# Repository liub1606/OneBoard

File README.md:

# OneBoard

OneBoard is a 20(ish) percent keyboard with a rotary encoder. It uses QMK firmware running on a RP2040.

## Features:
- 3D printed outer case
- EC11 Rotary encoder for volume and general media control.
- 19 Keys

## CAD Model:
We use 4 M3 Bolts and heatset inserts to put everything together. In total it has 2 separate peices.

Made using Onshape: https://cad.onshape.com/documents/e6a77505b9b66916f410a9e2/w/3fad1cba9b12220fb1d6acfb/e/3a9642192f18001e0b7e9c0b?renderMode=0&uiState=69bc452a0bbfb517c13afba3

## PCB
My PCB made in Kicad. I used KLE to design the keyboard layout and used a plugin to get everything laid out.

Schematic

PCB

## Firmware Overview
This keyboard uses [QMK](https://qmk.fm/) firmware for everything. 

- The rotary encoder changes volume, press the encoder to pause media.
- Basically acts like the left side of a full sized keyboard.

## BOM:
All the materials needed for this hackpad:
- 19x Cherry MX Switches (16 supplied by Hackclub)
- 19x DSA Keycaps (16 supplied by Hackclub)
- 4x M3x5x4 Heatset inserts
- 4x M3x16mm SHCS Bolts
- 20x 1N4148 DO-35 Diodes. (16 supplied by Hackclub)
- 1x EC11 Rotary Encoder (supplied by Hackclub)
- 1x XIAO RP2040 (supplied by Hackclub)
- 1x Case (2 printed parts)

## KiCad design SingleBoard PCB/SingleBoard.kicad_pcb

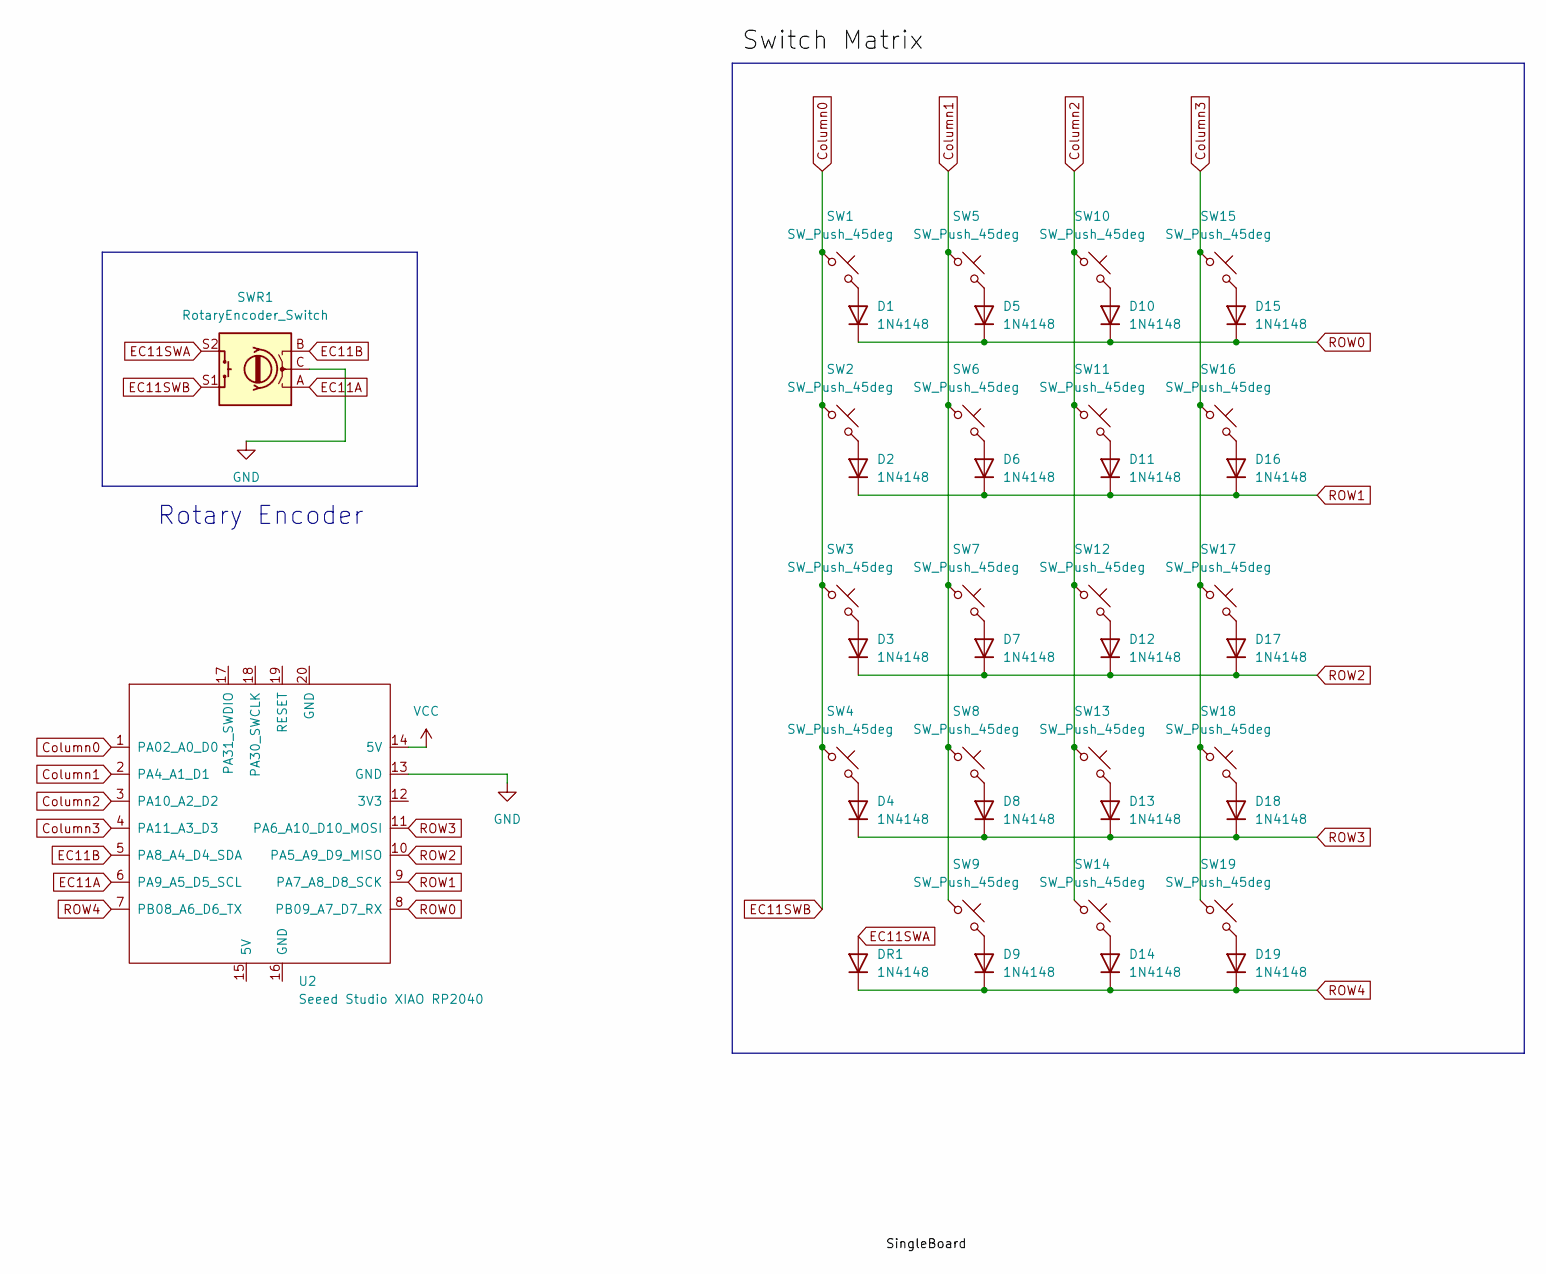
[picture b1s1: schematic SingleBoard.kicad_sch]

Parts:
D1, D2, D3, D4, D5, D6, D7, D8, D9, D10, D11, D12, D13, D14, D15, D16, D17, D18, D19: 1N4148; D_DO-35_SOD27_P7.62mm_Horizontal
DR1: 1N4148; D_DO-35_SOD27_P7.62mm_Horizontal
SW1, SW2, SW3, SW4, SW5, SW6, SW7, SW8, SW9, SW10, SW11, SW12, SW13, SW14, SW15, SW16, SW17, SW18, SW19: SW_Push_45deg; SW_Cherry_MX_1.00u_PCB
SWR1: RotaryEncoder_Switch; RotaryEncoder_Alps_EC11E-Switch_Vertical_H20mm
U2: Seeed Studio XIAO RP2040; XIAO-Generic-Hybrid-14P-2.54-21X17.8MM

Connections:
Column0: SW1.1, SW2.1, SW3.1, SW4.1, SWR1.S1, U2.1 (PA02_A0_D0)
Column1: SW5.1, SW6.1, SW7.1, SW8.1, SW9.1, U2.2 (PA4_A1_D1)
Column2: SW10.1, SW11.1, SW12.1, SW13.1, SW14.1, U2.3 (PA10_A2_D2)
Column3: SW15.1, SW16.1, SW17.1, SW18.1, SW19.1, U2.4 (PA11_A3_D3)
EC11A: SWR1.A, U2.6 (PA9_A5_D5_SCL)
EC11B: SWR1.B, U2.5 (PA8_A4_D4_SDA)
EC11SWA: DR1.2 (A), SWR1.S2
GND: SWR1.C, U2.13 (GND)
unnamed: D1.2 (A), SW1.2
unnamed: D2.2 (A), SW2.2
unnamed: D3.2 (A), SW3.2
unnamed: D4.2 (A), SW4.2
unnamed: D5.2 (A), SW5.2
unnamed: D6.2 (A), SW6.2
unnamed: D7.2 (A), SW7.2
unnamed: D8.2 (A), SW8.2
unnamed: D9.2 (A), SW9.2
unnamed: D10.2 (A), SW10.2
unnamed: D11.2 (A), SW11.2
unnamed: D12.2 (A), SW12.2
unnamed: D13.2 (A), SW13.2
unnamed: D14.2 (A), SW14.2
unnamed: D15.2 (A), SW15.2
unnamed: D16.2 (A), SW16.2
unnamed: D17.2 (A), SW17.2
unnamed: D18.2 (A), SW18.2
unnamed: D19.2 (A), SW19.2
ROW0: D1.1 (K), D5.1 (K), D10.1 (K), D15.1 (K), U2.8 (PB09_A7_D7_RX)
ROW1: D2.1 (K), D6.1 (K), D11.1 (K), D16.1 (K), U2.9 (PA7_A8_D8_SCK)
ROW2: D3.1 (K), D7.1 (K), D12.1 (K), D17.1 (K), U2.10 (PA5_A9_D9_MISO)
ROW3: D4.1 (K), D8.1 (K), D13.1 (K), D18.1 (K), U2.11 (PA6_A10_D10_MOSI)
ROW4: D9.1 (K), D14.1 (K), D19.1 (K), DR1.1 (K), U2.7 (PB08_A6_D6_TX)
VCC: U2.14 (5V)

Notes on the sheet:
Rotary Encoder

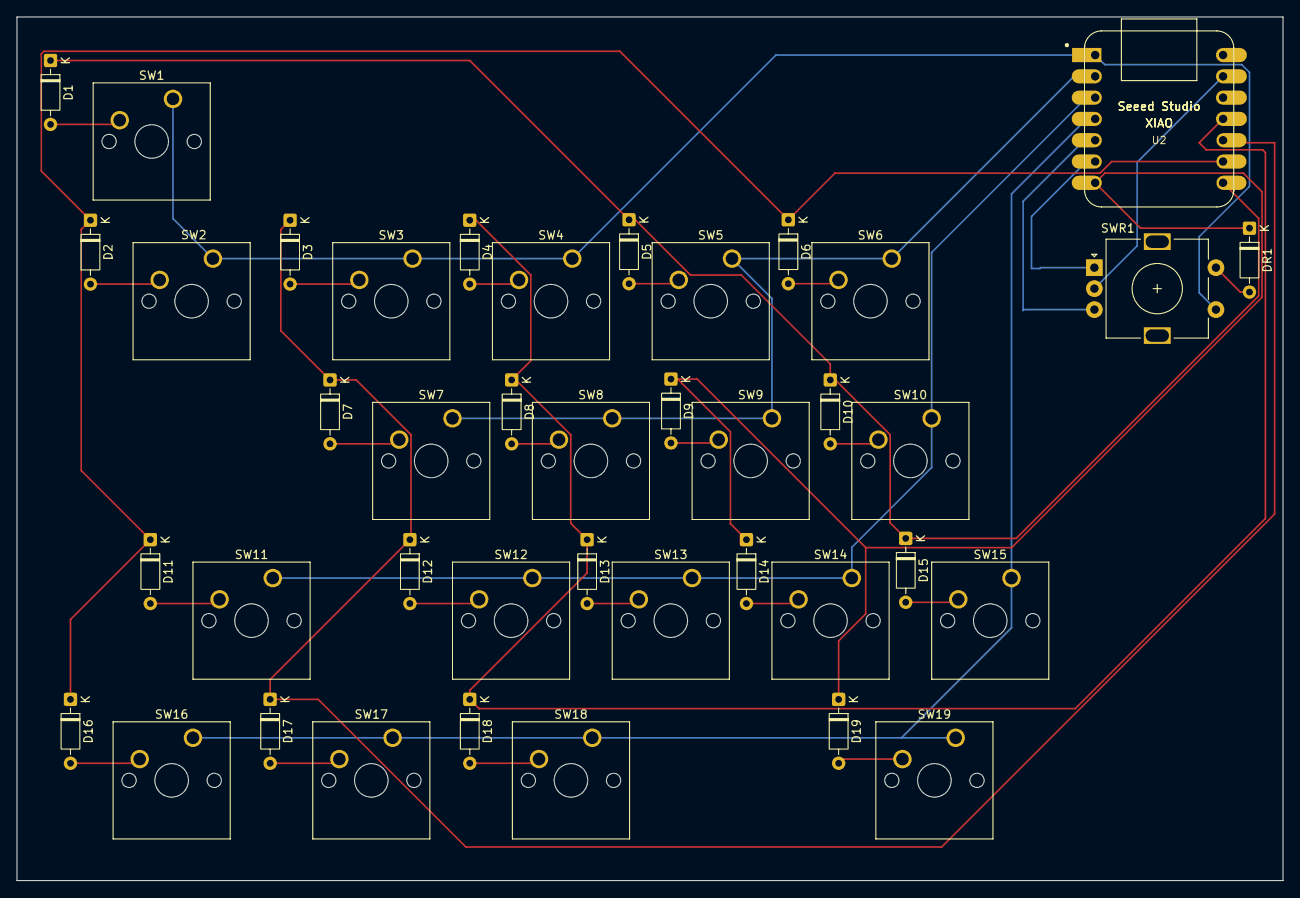
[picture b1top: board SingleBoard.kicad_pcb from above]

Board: 2 copper layers, 151.0 x 103.0 mm, 41 parts (0 on the bottom side), 32 nets.

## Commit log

2026-03-18 Created Pcb
2026-03-19 Added case files.
2026-03-19 Added production files.
2026-03-19 Made changes to case design and spacebar placement.
2026-03-19 Added mounting holes on pcb
2026-03-19 Fix PCB image path in README
    Corrected image path for PCB in README.
2026-03-19 Updated 3D files
2026-03-19 Revise OneBoard description and component details
    Updated keyboard description and clarified supplied components.
2026-03-19 Update README to clarify keyboard functionality
